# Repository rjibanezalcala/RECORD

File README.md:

# Welcome to RECORD!
The the REward-COst in Rodent Decision-making (RECORD) is a microcontroller-based system for the design and implementation of behavioural trials with the ability to synchronise with other external neural recording systems. RECORD has a variety of applications, but its main purpose is for behavioural neuroscience implementations.

The system offers modularity and customisability at its core. It includes 3D-printed components, electronics, and software.

[Check out our published paper on Nature Communications Biology!](https://doi.org/10.1038/s42003-024-06489-8)

## 3D printing
We have personally designed every 3D-printed component of the system, and have provided the [AutoCAD files](https://github.com/rjibanezalcala/RECORD/tree/main/3d-prints/cad) for editing, and the [STL files](https://github.com/rjibanezalcala/RECORD/tree/main/3d-prints/stl) for printing directly. 

## Electronic hardware and firmware
The electronics that drive the RECORD system are cheap but effective. We use an embedded systems approach to allow for customisable trials that can either be automated, or performed manually. The embedded electronics work on a command-servicing routine, which will make the electronics react to commands sent by the user via serial communications.

We chose the [Texas Instruments MSP430-FR2355 microcontroller](https://www.ti.com/tool/MSP-EXP430FR2355) due to its low price (~13 USD) and versatility. All of RECORD's [microcontroller firmware](https://github.com/rjibanezalcala/RECORD/tree/main/microcontroller) can be found within this repository.

Our custom-designed PCB is a hub for signals to be relayed from the microcontroller to our rodent arenas. We provide all [Gerber files](https://github.com/rjibanezalcala/RECORD/tree/main/pcb) in this repository.

## Software
Within this repository, you will find example scripts and workflows that can be used as templates for designing your own behavioural trials. For example, we have developed software packages designed specifically for our system. These packages allow scripting of customised trials in [Python](https://github.com/rjibanezalcala/RECORD/tree/main/python). We also provide [Ethovision experiments](https://github.com/rjibanezalcala/RECORD/tree/main/ethovision_experiments) and [Bonsai workflows](https://github.com/rjibanezalcala/RECORD/tree/main/bonsai_workflows) containing our custom decision making task.

Specifically for Ethovision, we provided [Batch scripts](https://github.com/rjibanezalcala/RECORD/tree/main/microcontroller/batch_scripts) that allow communication with our microcontroller system within an experiment's trial-control.

Data management is important for high-throughput systems, thus we created [Serendipity](https://github.com/lddavila/UTEP-Brain-Computation-Lab-Remote-Databases-and-Serendipity-App/tree/main/App%20Deployment%20Folder), a databasing and data pre-processing software suite, provided in an outside repository.

Finally, our data analysis software suite, including [behavioural feature extraction tools](https://github.com/atanugiri/Feature-Extraction), [neuroeconomic analysis tools](https://github.com/rjibanezalcala/RECORD/tree/main/data_analysis/neuroeconomic_analysis), [behavioural classification tools](https://github.com/lddavila/UTEP-Brain-Computation-Lab-Remote-Databases-and-Serendipity-App), are all provided within this and outside repositories.

trial_start_tone was created using [Tonegen](https://www.nch.com.au/tonegen/index.html).

## Documentation

The User Manual, Build guides, and other documentation can be found in our [documentation](https://github.com/rjibanezalcala/RECORD/tree/main/documentation) section.
<!--
> Written with [StackEdit](https://stackedit.io/).
-->
<!--stackedit_data:
eyJoaXN0b3J5IjpbMTIzNTUwMDI1Nl19
-->

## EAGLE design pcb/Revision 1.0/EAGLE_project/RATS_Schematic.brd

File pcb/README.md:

# Welcome to RECORD/pcb!
Our custom PCB was designed using [Autodesk EAGLE](http://eagle.autodesk.com/). We have provided our projects as a Zip file for importing into EAGLE and making modifications, as well as the Gerber files we used for printing the board. 
## Our custom Printed Circuit Board (PCB)
The printed circuit board serves as a relay center for the various signals that the RECORD hardware needs for function. It also houses various JST connectors to ensure secure connection of the different cable assemblies. Every component on the PCB is through-hole, useful for manual soldering of each component. 
## Resistor values
Resistor values depend mostly on the LEDs chosen for the system. They are mainly for stepping a higher voltage signal down for protection of the LEDs. The voltage divider section is used for protection of the microcontroller, in case input TTL signals cannot be adjusted to the microcontroller's operating range.

> Written with [StackEdit](https://stackedit.io/).
<!--stackedit_data:
eyJoaXN0b3J5IjpbMzA1NjkyMDExLDQxMzA1NjI3NF19
-->

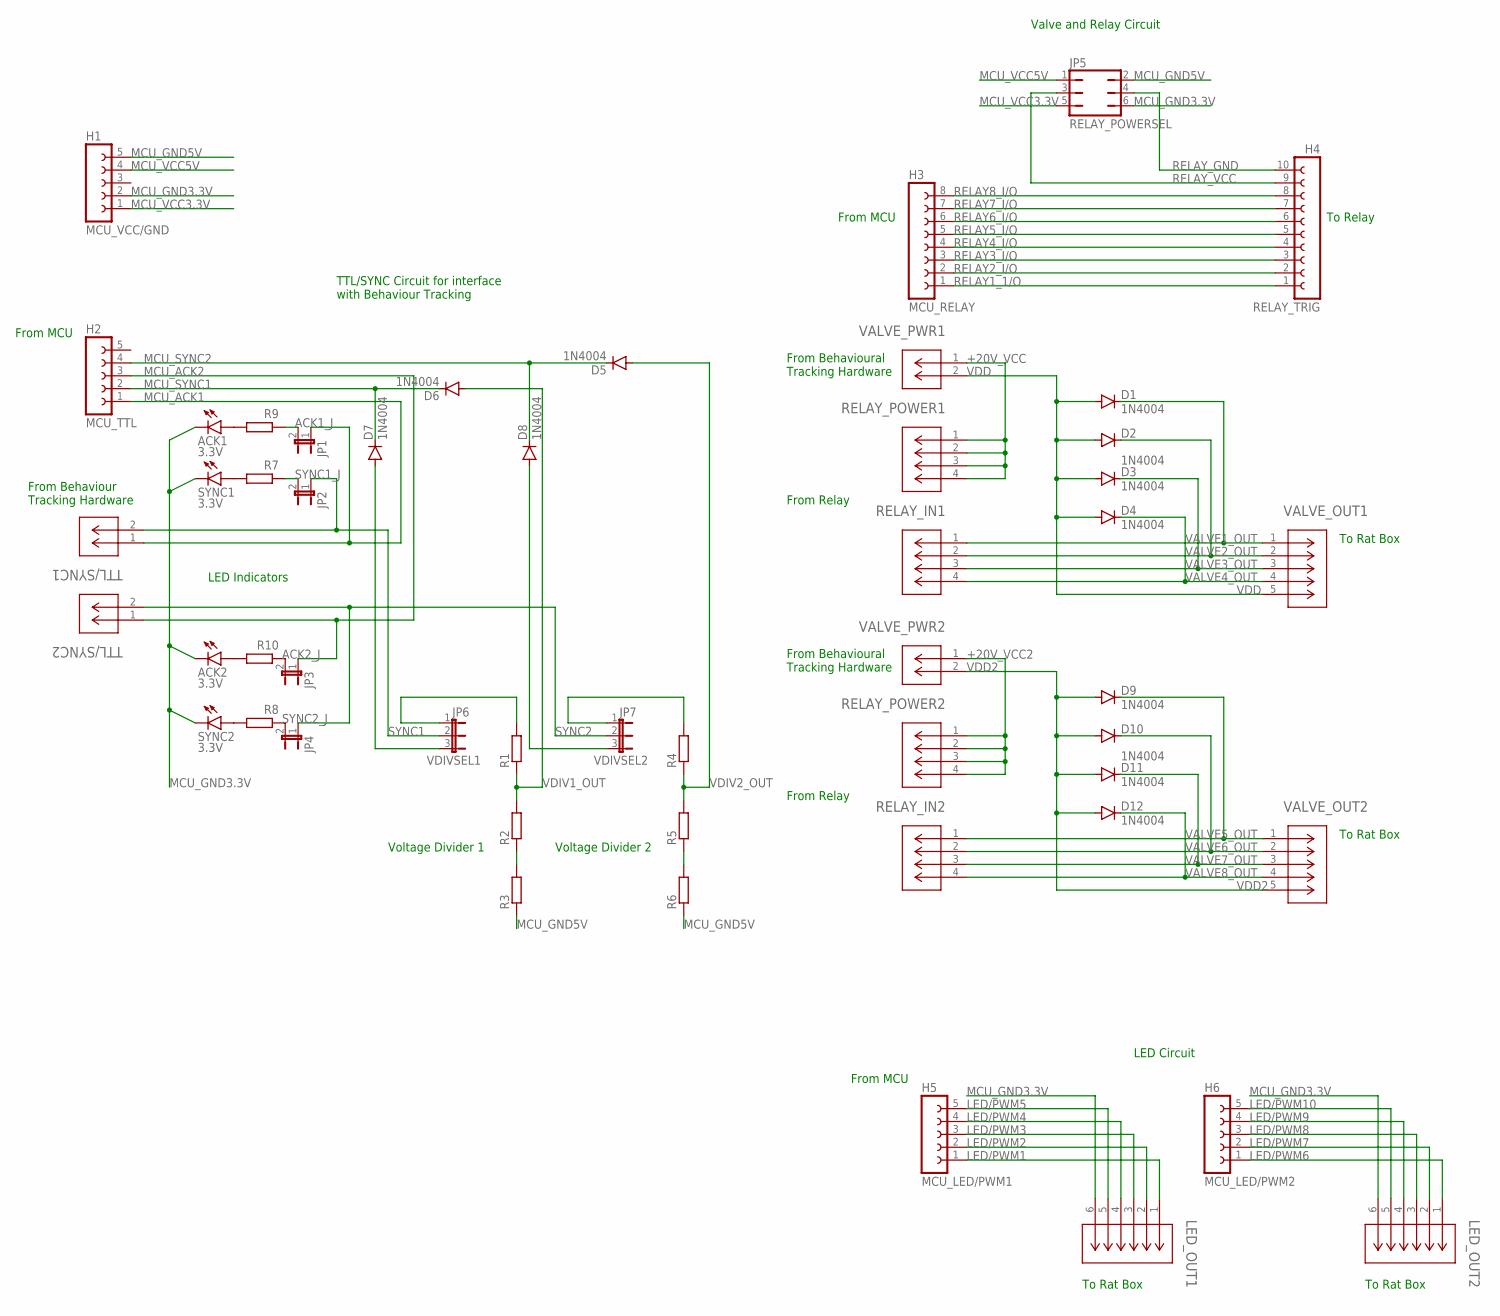
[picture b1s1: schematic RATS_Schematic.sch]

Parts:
ACK1, ACK2: 3.3V; LED5MM
D1, D2, D3, D4, D5, D6, D7, D8, D9, D10, D11, D12: 1N4004; DO41-10
H1: MCU_VCC/GND; FE05-1
H2: MCU_TTL; FE05-1
H3: MCU_RELAY; FE08
H4: RELAY_TRIG; FE10
H5: MCU_LED/PWM1; FE05-1
H6: MCU_LED/PWM2; FE05-1
JP1: ACK1_J; JP1
JP2: SYNC1_J; JP1
JP3: ACK2_J; JP1
JP4: SYNC2_J; JP1
JP5: RELAY_POWERSEL; JP3Q
JP6: VDIVSEL1; JP2
JP7: VDIVSEL2; JP2
LED_OUT1, LED_OUT2: B6B-XH-A(LF)(SN); CONN_B6B-XH-A(LF)(SN)_JST
R1, R2, R3, R4, R5, R6, R7, R8, R9, R10: R-EU_0204/7; 0204/7
RELAY_IN1, RELAY_IN2: B4B-XH-A_(LF)(SN); CONN_B4B-XH-A_(LF)(SN)_JST
RELAY_POWER1, RELAY_POWER2: B4B-XH-A_(LF)(SN); CONN_B4B-XH-A_(LF)(SN)_JST
SYNC1, SYNC2: 3.3V; LED5MM
TTL/SYNC1, TTL/SYNC2: B2B-XH-A(LF)(SN); CONN_B2B-XH-A(LF)(SN)_JST
VALVE_OUT1, VALVE_OUT2: B5B-XH-A(LF)(SN); CONN_B5B-XH-A(LF)(SN)_JST
VALVE_PWR1, VALVE_PWR2: B2B-XH-A(LF)(SN); CONN_B2B-XH-A(LF)(SN)_JST

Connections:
+20V_VCC: RELAY_POWER1.1, RELAY_POWER1.2, RELAY_POWER1.3, RELAY_POWER1.4, VALVE_PWR1.1
+20V_VCC2: RELAY_POWER2.1, RELAY_POWER2.2, RELAY_POWER2.3, RELAY_POWER2.4, VALVE_PWR2.1
LED/PWM1: H5.1, LED_OUT1.1
LED/PWM2: H5.2, LED_OUT1.2
LED/PWM3: H5.3, LED_OUT1.3
LED/PWM4: H5.4, LED_OUT1.4
LED/PWM5: H5.5, LED_OUT1.5
LED/PWM6: H6.1, LED_OUT2.1
LED/PWM7: H6.2, LED_OUT2.2
LED/PWM8: H6.3, LED_OUT2.3
LED/PWM9: H6.4, LED_OUT2.4
LED/PWM10: H6.5, LED_OUT2.5
MCU_ACK1: H2.1, JP1.1, TTL/SYNC1.1
MCU_ACK2: H2.3, JP3.1, TTL/SYNC2.1
MCU_GND3.3V: ACK1.K (C), ACK2.K (C), H1.2, JP5.6, LED_OUT1.6, LED_OUT2.6, SYNC1.K (C), SYNC2.K (C)
MCU_GND5V: H1.5, JP5.2, R3.1, R6.1
MCU_SYNC1: D6.C, D7.C, H2.2
MCU_SYNC2: D5.C, D8.C, H2.4
MCU_VCC3.3V: H1.1, JP5.5
MCU_VCC5V: H1.4, JP5.1
unnamed: R7.2, SYNC1.A
unnamed: R8.2, SYNC2.A
unnamed: R2.1, R3.2
unnamed: JP6.1, R1.2
unnamed: D7.A, JP6.3
unnamed: D8.A, JP7.3
unnamed: JP7.1, R4.2
unnamed: ACK1.A, R9.2
unnamed: R5.1, R6.2
unnamed: ACK2.A, R10.2
unnamed: JP2.2, R7.1
unnamed: JP1.2, R9.1
unnamed: JP3.2, R10.1
unnamed: JP4.2, R8.1
RELAY1_1/O: H3.1, H4.1
RELAY2_I/O: H3.2, H4.2
RELAY3_I/O: H3.3, H4.3
RELAY4_I/O: H3.4, H4.4
RELAY5_I/O: H3.5, H4.5
RELAY6_I/O: H3.6, H4.6
RELAY7_I/O: H3.7, H4.7
RELAY8_I/O: H3.8, H4.8
RELAY_GND: H4.10, JP5.4
RELAY_VCC: H4.9, JP5.3
SYNC1: JP2.1, JP6.2, TTL/SYNC1.2
SYNC2: JP4.1, JP7.2, TTL/SYNC2.2
VALVE1_OUT: D1.C, RELAY_IN1.1, VALVE_OUT1.1
VALVE2_OUT: D2.C, RELAY_IN1.2, VALVE_OUT1.2
VALVE3_OUT: D3.C, RELAY_IN1.3, VALVE_OUT1.3
VALVE4_OUT: D4.C, RELAY_IN1.4, VALVE_OUT1.4
VALVE5_OUT: D9.C, RELAY_IN2.1, VALVE_OUT2.1
VALVE6_OUT: D10.C, RELAY_IN2.2, VALVE_OUT2.2
VALVE7_OUT: D11.C, RELAY_IN2.3, VALVE_OUT2.3
VALVE8_OUT: D12.C, RELAY_IN2.4, VALVE_OUT2.4
VDD: D1.A, D2.A, D3.A, D4.A, VALVE_OUT1.5, VALVE_PWR1.2
VDD2: D9.A, D10.A, D11.A, D12.A, VALVE_OUT2.5, VALVE_PWR2.2
VDIV1_OUT: D6.A, R1.1, R2.2
VDIV2_OUT: D5.A, R4.1, R5.2

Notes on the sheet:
LED Indicators
From MCU
From Behaviour Tracking Hardware
Voltage Divider 1
Voltage Divider 2
From Behavioural Tracking Hardware
From Relay
To Relay
To Rat Box
TTL/SYNC Circuit for interface with Behaviour Tracking
Valve and Relay Circuit
LED Circuit

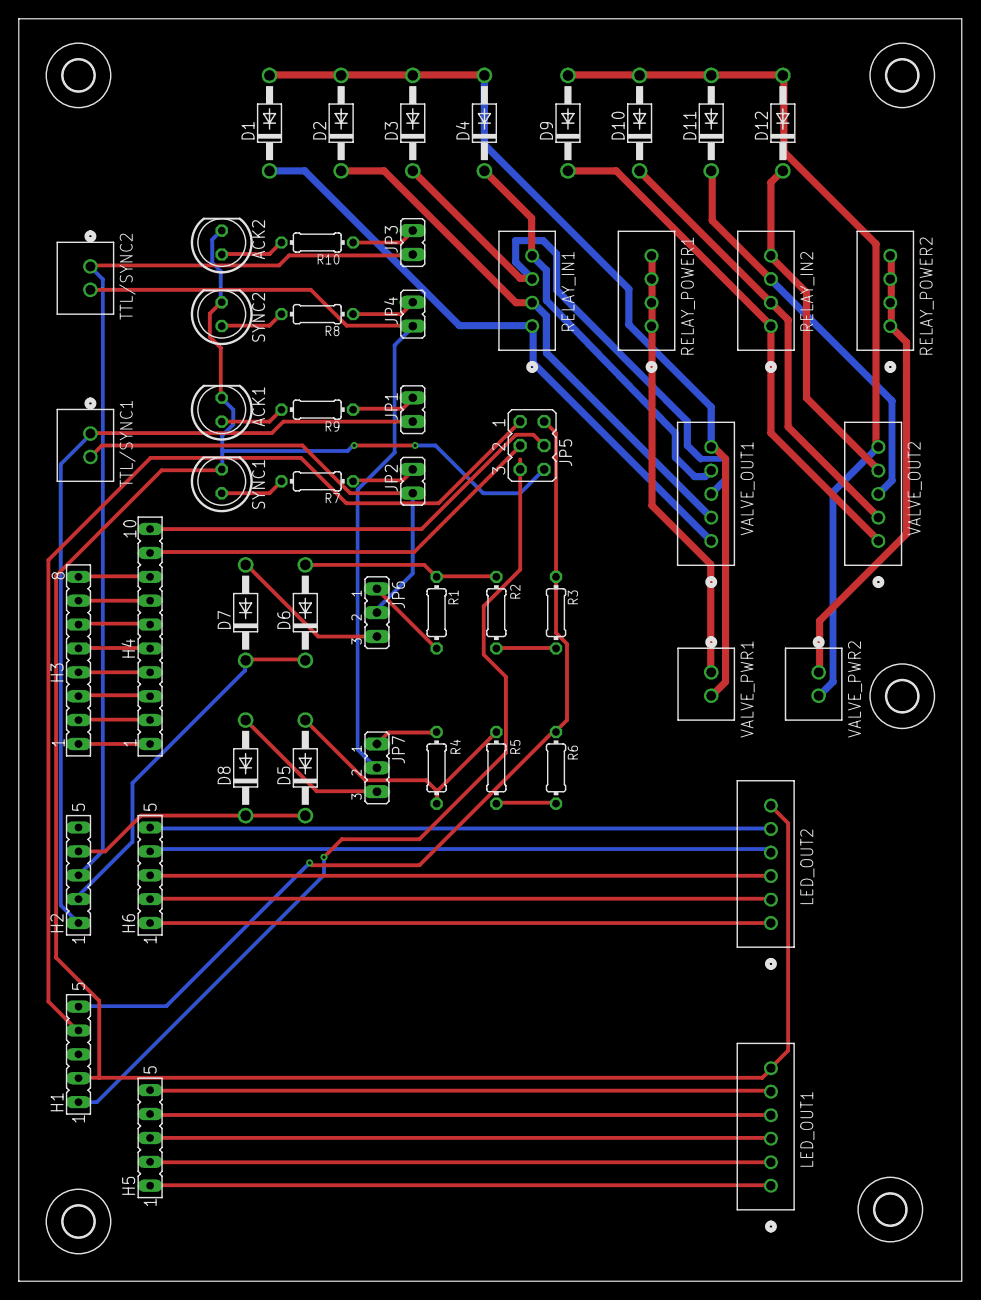
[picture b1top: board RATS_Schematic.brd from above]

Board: 2 copper layers, 100.3 x 134.3 mm, 56 parts (0 on the bottom side), 58 nets.

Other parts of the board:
U$1, U$2, U$3, U$4, U$5: 3,3

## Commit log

2023-03-02 Raquel added temporary files to gitignore
2023-03-02 Raquel created the python folder
2023-03-02 Raquel created the microcontroller folder
2023-03-02 Raquel created the matlab folder
2023-03-02 Renamed folder
2023-03-27 Raquel deleted unnecessary folder
2023-05-01 Raquel uploaded files
    Initial commit of files.
2023-05-01 Raquel added more files
2023-05-01 Raquel added even more files
2023-05-02 Added folder
2023-05-03 Added D's neuroeconomic analysis files
2023-05-12 Create ethovision folder
2023-05-12 Added bonsai folder
2023-05-12 Create documentation folder
2023-05-12 Create matlab_library
2023-06-02 main/python/pythonREADME.md created from https://stackedit.io/
2023-06-02 python/README.md updated from https://stackedit.io/
2023-06-02 README.md updated from https://stackedit.io/
2023-06-02 pcb/Revision 1.0/README.md created from https://stackedit.io/
2023-06-02 microcontroller/README.md.md created from https://stackedit.io/
2023-06-02 3d-prints/README.md created from https://stackedit.io/
2023-06-02 bonsai_workflows/README.md created from https://stackedit.io/
2023-06-02 pcb/README.md created from https://stackedit.io/
2023-06-02 pcb/README.md updated from https://stackedit.io/
2023-09-27 Update README.md
    fixed typo
2023-10-12 microcontroller/mcuREADME created from https://stackedit.io/
2023-10-12 microcontoller/mcuREADME.md created from https://stackedit.io/
2023-10-12 microcontroller/mcuREADME.md created from https://stackedit.io/
2024-03-12 Updated user manual
    Added small section about Ethovision trial events and delays.
2024-07-12 Create LICENSE
2024-10-11 Update LICENSE
2025-07-15 Version 2.2.1
    Added support for parsing multiple light commands at the same time. Example usage: "#F1L3F2L1F3L2F4L1"; this will turns feeder1 to level 3, 2 and 4 to level 1, and 3 to level 2. If driving less than 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

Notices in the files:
parts and their libraries:
COPYRIGHT: Copyright (C) 2021 Ultra Librarian. All rights reserved.
